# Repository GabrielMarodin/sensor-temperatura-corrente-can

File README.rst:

Monitoramento de temperatura e corrente via CAN do barco solar
#####################################################################

.. contents::
   :local:
   :depth: 2

Requisitos
**********

Este projeto foi implementado com os seguintes módulos/softwares/hardwares:
 | Sensor de temperatura PT100 com 3 fios.    
 | Sensor de corrente de efeito Hall LEM LA 205-S.  
 | MCP2515 (Controlador CAN);
 | TJA1050 (Transceptor CAN);  
 | Linguagem de programação C.  
 | Microcontrolador STM32F401 com SPI, ADC e regulador de 5V para 3V3.  

Visão geral
***********

Esse projeto faz parta do barco solar Zênite Solar.

.. figure:: /images/pcb_3dmodel.png
   :alt: Modelo 3D da placa de circuito impresso
   :align: center
   :name: 3D model of PCB.

É um sistema microcontrolado embarcado ao barco que possui capacidade de ler temperaturas em pontos estratégicos do barco e a corrente do motor.

O microcontrolador lê e trata os dados e empacota em um frame CAN para transmitir, através a implementação do controlador e transmissor CAN, para a saída do conector RJ45.

O desenvolvimento foi divido em quatro etapas:

- `Etapa 1 </etapa_1>`_ (02/04/2026): Pesquisa, planejamento e outline do projeto.
- `Etapa 2 </etapa_2>`_ (30/04/2026): Teste dos módulos e desenvolvimento de protótipo.
- `Etapa 3 </etapa_3>`_ (28/05/2026): Desenvolvimento do produto.
- `Etapa 4 </etapa_4>`_ (09/07/2026): Implementação e análise de desempenho.

Interface do usuário
********************
LED de respiração:
  Pisca enquanto o RTOS estiver ativo.

Testando
========

Para testar pode ser usado o debugger do microcontrolador para ler as variáveis e registradores ou um analizador de CAN para capturar as mensagens transmitidas.

Montagem
********

O sistema é alimentado e transmite os frames CAN pelo conector RJ45;

O sensor de corretente de efeito hall deve ser conectado no conector de 4 pinos;

O PT100 deve ser conectado no MAX31865 nos conectores de parafuso.

.. figure:: /images/max_3wired.jpg
   :alt: MAX31865 breakout board com 3 fios conectados
   :align: center
   :name: MAX31865 connection

   Modo de conexão de 3 fios do PT100.

   No modo 3 wires 2 fios estão em paralelo e 1 fio tem 100 ohms de resistência a 0 graus celsius em relação aos outros, os fios com resistência muito baixa entre si devem ser conectados em RTD+ e F+, enquanto o terceiro fio deve ser conectado em RTD-.

Referências (Links)
*******************

- `GitHub do Zênite Solar <https://github.com/ZeniteSolar>`_

- `Firmware do Projeto </etapa_4/Firmware>`_

- `Projeto KiCad da PCB </etapa_3/PCB/Modulo_corrente_temperatura_barco_Zenite>`_

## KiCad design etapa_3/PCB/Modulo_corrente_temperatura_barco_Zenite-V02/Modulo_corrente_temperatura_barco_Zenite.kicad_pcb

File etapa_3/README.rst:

Etapa 3
#######

.. contents::
   :local:
   :depth: 2

Visão geral
***********

A Etapa 3 abordará a implementação do protocolo CAN, bem como a integração e os testes dos dados provenientes dos sensores em um mesmo firmware baseado em arquitetura RTOS. O objetivo é validar o envio correto das informações pelo barramento CAN.

Além disso, será abordado a elaboração do esquemático da placa de circuito impresso, juntamente com a definição dos critérios de desempenho do sistema, que serão avaliados na etapa seguinte.

Desenvolvimento
***************

`Link para os Testes <Testes>`_

Implementação do Protocolo CAN
==============================

O `driver </etapa_3/Testes/pi3_CAN_test/Core/Src/MCP2515_driver.c>`_ do MCP2515 se baseia na implementação da Microchip e utiliza o mapa de registradores do  `datasheet <https://ww1.microchip.com/downloads/en/DeviceDoc/MCP2515-Stand-Alone-CAN-Controller-with-SPI-20001801J.pdf>`_ (tabelas 11-1 e 11-2).
O MCP2515 é configurado para ter sua divisão de clock de 8 MHz de forma a transmitir em 500 Kbps;

Integração dos dados dos sensores à aplicação
=============================================

Os dados dos sensores foram arranjados da seguinte maneira:

Temperatura:

+-------------------+----------------+
|        Dado       | Tamanho (Bits) |
+===================+================+
|    Temp. Motor    |       10       |
+-------------------+----------------+
| Temp. Controlador |       9        |
+-------------------+----------------+
|   Temp. Bateria   |       10       |
+-------------------+----------------+
|  Falha Detectada  |        3       |
+-------------------+----------------+

Foi alterado para possibilitar o relatório de erro individual de cada sensor.

Corrente:

+---------------------+----------------+
| Dado                | Tamanho (Bits) |
+=====================+================+
| Corrente de Pico    | 12             |
+---------------------+----------------+
| Sentido do Pico     | 1              |
+---------------------+----------------+
| Corrente RMS        | 12             |
+---------------------+----------------+
| Sentido da Corrente | 1              |
+---------------------+----------------+
| Mensagem de Erro    | 7              |
+---------------------+----------------+

Estes dados foram integrados em pacotes com o seguinte código:

`sensor de corrente </etapa_3/Firmware/Core/Inc/current_sensor.h>`_:

.. code-block:: C

	typedef struct __attribute__((packed)) {
      uint32_t Peak_Current : 11; // Corrente de Pico
      uint32_t Peak_Dir     : 1;  // Sentido da Corrente de Pico
      uint32_t Current_RMS  : 12; // Corrente RMS
      uint32_t Current_Dir  : 1;  // Direção Principal da Corrente
      uint32_t Error_msg    : 7;  // Mensagens de Erro
   } Current_pkg;

`sensores de temperatura </etapa_3/Firmware/Core/Inc/temperature_sensor.h>`_:

.. code-block:: C

   typedef struct __attribute__((packed)) {
      uint32_t Motor_Temp  : 10; // Temperatura do Motor
      uint32_t Charge_Temp : 9;  // Temperatura dos Controladores de Carga
      uint32_t Batt_Temp   : 10; // Temperatura da Bateria
      uint32_t Error_msg   : 3;  // Mensagens de Erro
   } Temp_pkg;

- `Link para o firmware </etapa_3/Firmware>`_

Teste da Rede CAN com Dados dos Sensores
========================================
Após implementação em código do `sensor de corrente </etapa_3/Testes/Sensor_RTOS/Core/Src/Current_Sensor.c>`_ 
e dos `sensores de temperatura </etapa_3/Testes/Sensor_RTOS/Core/Src/Temperature_Sensor.c>`_, foi implementada 
à partir do `driver do MCP2515 </etapa_3/Testes/Sensor_RTOS/Core/Src/MCP2515_Driver.c>`_ a transmição dos 
dados dos sensores utilizando o protocolo CAN nos IDS 0x10 e 0x11. O teste foi realizado utilizando um 
`ESP 32 </etapa_3/Testes/ESP32devkit/ESP32MCP2515>`_ como nó receptor, com o blackpill STM atuando como 
nó transmissor enviando mensagens.

Segue uma imagem do teste da rede CAN, o osciloscópio mede a tensão diferencial da linha no módulo utilizado.

.. image:: images/can_test.png
   :scale: 30 %

O ESP32 foi configurado para repassar as mensagems que recebe por SPI do MCP2515 para a porta 
serial, e o terminal do computador foi configurado para receber as mensagens. Devido à um problema de comunicação,
não foi possível realizar a leitura da rede CAN.

Esquemático da PCI
==================

O projeto KiCad onde foi elaborado o esquemático pode ser encontrado em:  `Link para o Esquemático do Projeto <https://github.com/GabrielMarodin/sensor-temperatura-corrente-can/tree/main/etapa_3/PCB/Modulo_corrente_temperatura_barco_Zenite>`_ 

O esquemático apresentado em partes nos próximos tópicos foi desenvolvido para atender aos requisitos do projeto, considerando:

- Níveis de tensão e corrente necessários para cada sensor e circuito integrado.

.. image:: images/Esquematico_potencia.png
	:scale: 30%

Na figura acima é possível observar elementos de proteção contra sobrecorrente e surtos de tensão, além de um regulador linear destinado à alimentação do microcontrolador e de um conversor estático responsável por suprir as necessidades do sensor de corrente utilizado.

- Conexão com a rede CAN, alimentação do módulo e do sensor de corrente.

.. image:: images/Esquematico_conectores.png
	:scale: 30%

Além dos conectores RJ45 padrão do barco foi necessário a previsão de um conector 3 pinos genérico para a alimentação e retorno do sinal em corrente do LA 205-s.

- Condicionamento do sinal de corrente do LA 205-s.

.. image:: images/Esquematico_condicionamento_sinal.png
	:scale: 30%

Observa-se na figura a presença de amplificadores operacionais configurados em diferentes topologias: buffer (para sinal de referência), somador não inversor (para obtenção do offset) e filtro ativo passa-baixa de segunda ordem.

   O circuito funciona de modo que:

   - 1,65 V na saída representam 0 A;
   - 3,3 V na saída correspondem a +200 A;
   - 0 V na saída equivalem a –200 A.
 
Ressalta-se que, atualmente, a frequência de corte do filtro encontra-se próxima de 120 kHz. No entanto, essa configuração pode ser ajustada posteriormente, mediante análise da forma de onda real da corrente do motor.

- Gerenciamento e envio de mensagens CAN.

.. image:: images/Esquematico_CAN.png
	:scale: 30%

Na figura acima obeserva-se os CIs responsáveis pelo gerenciamento do protocolo e transdução do sinal.

- Processamento de dados e transdução da temperatura.

.. image:: images/Esquematico_microcontrolador.png
	:scale: 30%

Na figura acima observa-se a atribuição dos pinos no microcontrolador, além dos três módulos baseados no circuito integrado MAX31865. Ressalta-se que existe a possibilidade de substituir os módulos pelo próprio CI, entretanto, devem ser consideradas as restrições de fabricação da placa em virtude do encapsulamento do MAX31865.

Critérios de Desempenho
***********************

Os critérios de desempenho adotados para o projeto, que deverão ser medidos na próxima etapa, são:

- Tempo de execução de cada tarefa;
- Tempo de ocupação da CPU;
- Medição do WCET (Worst-Case Execution Time);
- Eficiência energética da placa;
- Exatidão das medidas de corrente e temperatura, para fins de validação do código.

Referências (links/datasheets/livros)
*************************************

- `Código de interface MCP2515 <https://github.com/eziya/STM32_SPI_MCP2515/tree/master>`_

- `Datasheet do MCP2515 <https://www.microchip.com/en-us/product/mcp2515>`_

- `GitHub do Zenite Solar <https://github.com/ZeniteSolar>`_

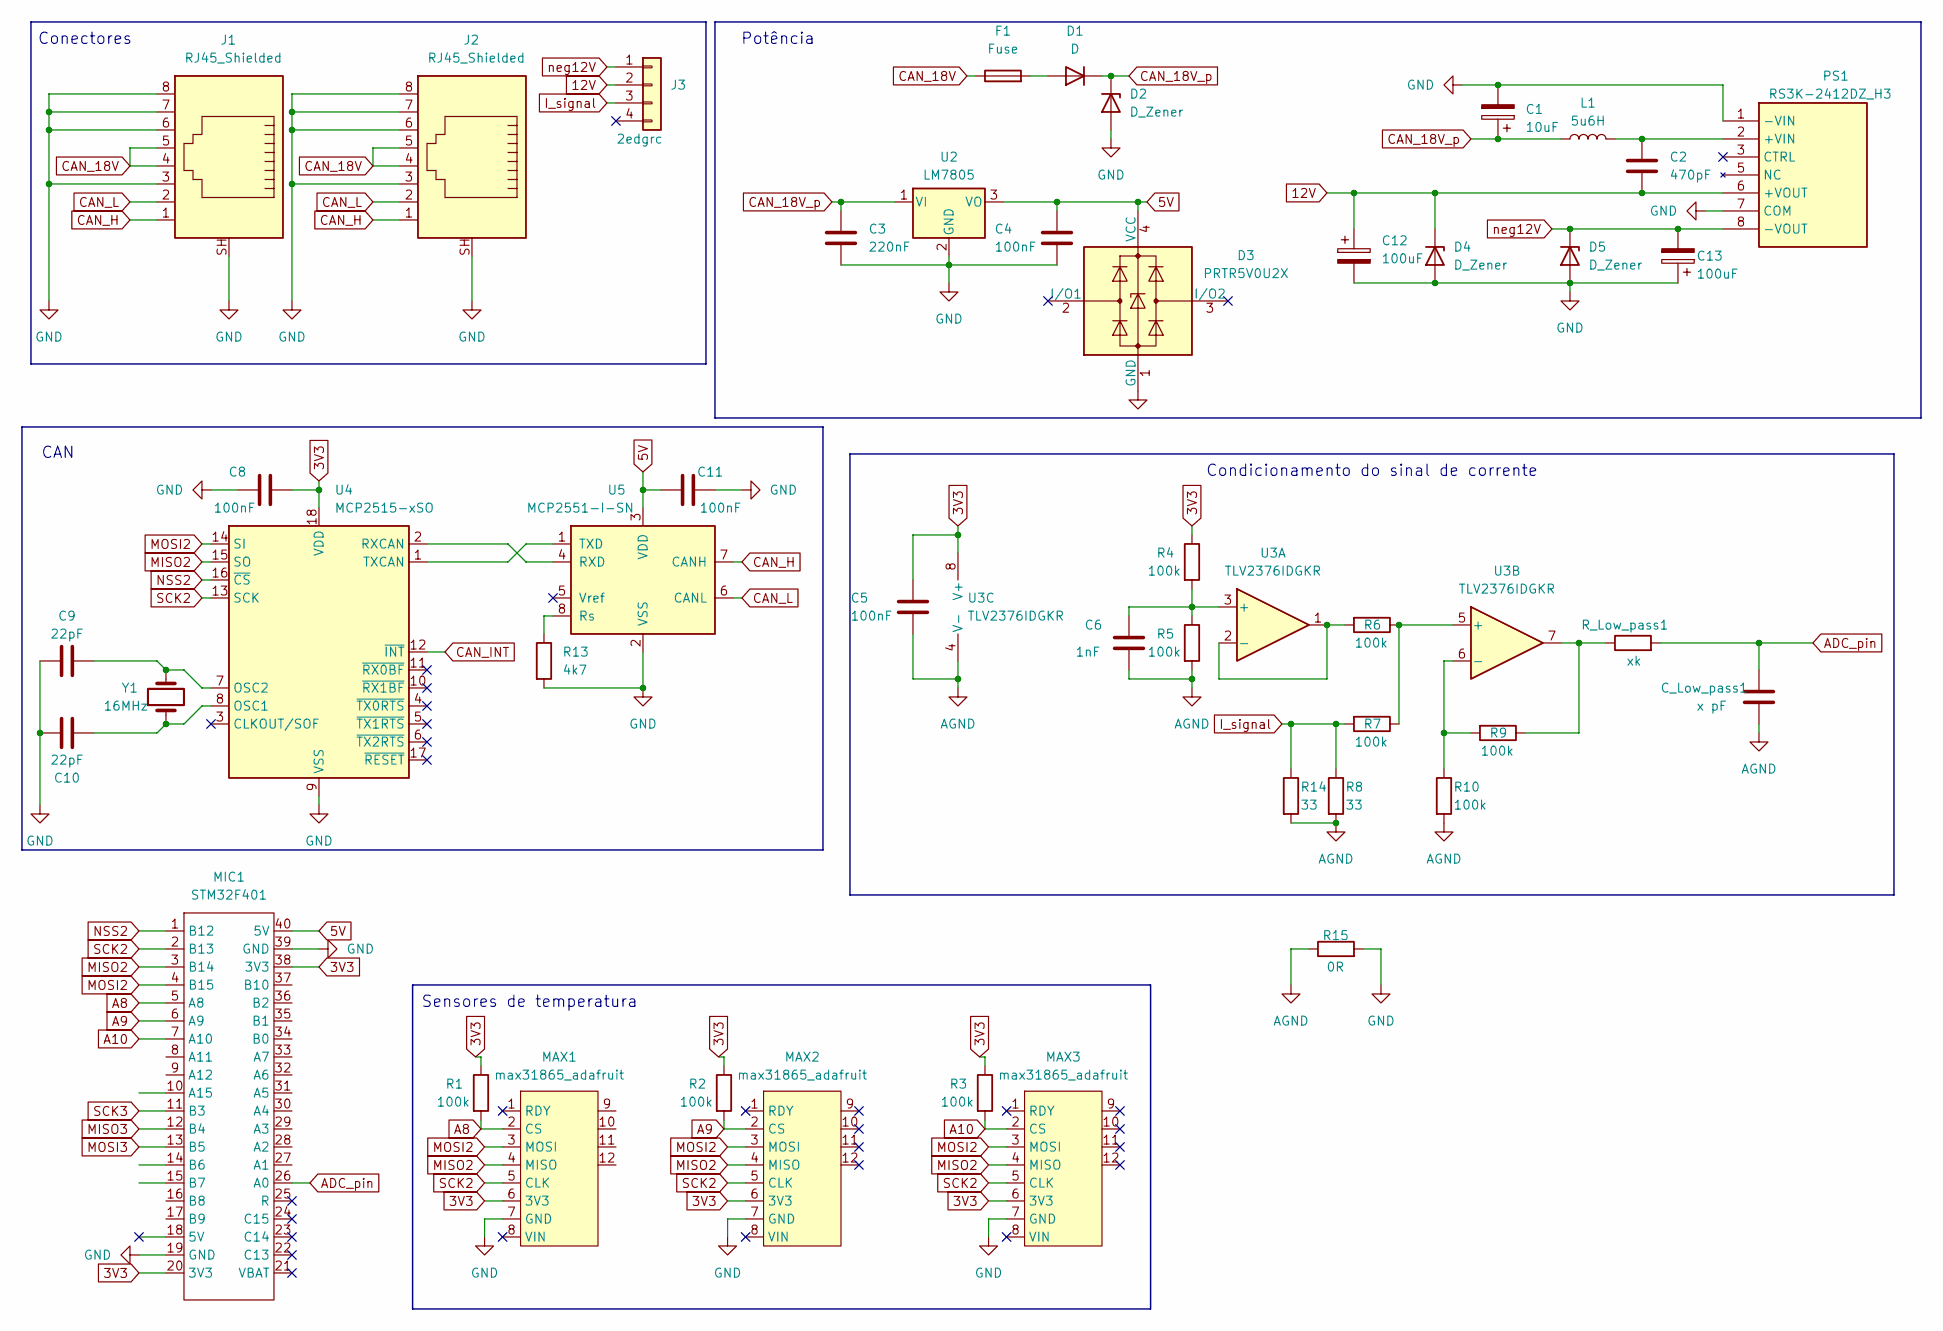
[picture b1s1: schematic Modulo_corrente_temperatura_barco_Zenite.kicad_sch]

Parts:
C1: 10uF; CP_Radial_D6.3mm_P2.50mm
C2: 470pF; C_0805_2012Metric_Pad1.18x1.45mm_HandSolder
C3: 220nF; C_0805_2012Metric_Pad1.18x1.45mm_HandSolder
C4, C5, C8, C11: 100nF; C_0805_2012Metric_Pad1.18x1.45mm_HandSolder
C6: 1nF; C_0805_2012Metric_Pad1.18x1.45mm_HandSolder
C9, C10: 22pF; C_0805_2012Metric_Pad1.18x1.45mm_HandSolder
C12, C13: 100uF; CP_Radial_D6.3mm_P2.50mm
C_Low_pass1: x pF; C_0805_2012Metric_Pad1.18x1.45mm_HandSolder
D1: D; D_5W_P10.16mm_Horizontal
D2: D_Zener; D_5W_P10.16mm_Horizontal
D3: PRTR5V0U2X; SOT-143_Handsoldering
D4, D5: D_Zener; D_SOD-123
F1: Fuse; fuse_holder
J1, J2: RJ45_Shielded; TE_RJ45-8N-B
J3: 2edgrc; 2EDRC_4pins
L1: 5u6H; ASPI0630LR5R6MT15
MAX1, MAX2, MAX3: max31865_adafruit; max31868_module
MIC1: STM32F401; BlackPill
PS1: RS3K-2412DZ_H3; RS3K2412DZH3; Manufacturer_Part_Number RS3K-2412DZ/H3
R1, R2, R3: 100k; R_Axial_DIN0207_L6.3mm_D2.5mm_P10.16mm_Horizontal
R4, R5, R6, R7, R9, R10: 100k; R_1206_3216Metric_Pad1.30x1.75mm_HandSolder
R8, R14: 33; R_1206_3216Metric_Pad1.30x1.75mm_HandSolder
R13: 4k7; R_0805_2012Metric_Pad1.20x1.40mm_HandSolder
R15: 0R; R_0805_2012Metric_Pad1.20x1.40mm_HandSolder
R_Low_pass1: xk; R_0805_2012Metric_Pad1.20x1.40mm_HandSolder
U2: LM7805; TO-220-3_Horizontal_TabDown
U3: TLV2376IDGKR; VSSOP-8_3x3mm_P0.65mm
U4: MCP2515-xSO; SOIC-18W_7.5x11.6mm_P1.27mm
U5: MCP2551-I-SN; SOIC-8_3.9x4.9mm_P1.27mm
Y1: 16MHz; Crystal_HC50_Vertical

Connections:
3V3: C5.1, C8.2, MAX1.6 (3V3), MAX2.6 (3V3), MAX3.6 (3V3), MIC1.20 (3V3), MIC1.38 (3V3), R1.1, R2.1, R3.1, R4.1, U3.8 (V+), U4.18 (VDD)
5V: C4.1, C11.1, D3.4 (VCC), MIC1.40 (5V), U2.3 (VO), U5.3 (VDD)
12V: C2.2, C12.1, D4.1 (K), J3.2, PS1.6 (+VOUT)
A8: MAX1.2 (CS), MIC1.5 (A8), R1.2
A9: MAX2.2 (CS), MIC1.6 (A9), R2.2
A10: MAX3.2 (CS), MIC1.7 (A10), R3.2
ADC_pin: C_Low_pass1.1, MIC1.26 (A0), R_Low_pass1.2
AGND: C5.2, C6.2, C_Low_pass1.2, R5.2, R8.2, R10.2, R14.2, R15.1, U3.4 (V-)
CAN_18V: F1.1, J1.4, J1.5, J2.4, J2.5
CAN_18V_p: C1.1, C3.1, D1.1 (K), D2.1 (K), L1.1, U2.1 (VI)
CAN_H: J1.1, J2.1, U5.7 (CANH)
CAN_INT: U4.12 (~INT)
CAN_L: J1.2, J2.2, U5.6 (CANL)
GND: C1.2, C3.2, C4.2, C8.1, C9.1, C10.1, C11.2, C12.2, C13.1, D2.2 (A), D3.1 (GND), D4.2 (A), D5.2 (A), J1.3, J1.6, J1.7, J1.8, J1.SH, J2.3, J2.6, J2.7, J2.8, J2.SH, MAX1.7 (GND), MAX2.7 (GND), MAX3.7 (GND), MIC1.19 (GND), MIC1.39 (GND), PS1.1 (-VIN), PS1.7 (COM), R13.2, R15.2, U2.2 (GND), U4.9 (VSS), U5.2 (VSS)
I_signal: J3.3, R7.2, R8.1, R14.1
MISO2: MAX1.4 (MISO), MAX2.4 (MISO), MAX3.4 (MISO), MIC1.3 (B14), U4.15 (SO)
MISO3: MIC1.12 (B4)
MOSI2: MAX1.3 (MOSI), MAX2.3 (MOSI), MAX3.3 (MOSI), MIC1.4 (B15), U4.14 (SI)
MOSI3: MIC1.13 (B5)
NSS2: MIC1.1 (B12), U4.16 (~CS)
unnamed: D1.2 (A), F1.2
unnamed: C2.1, L1.2, PS1.2 (+VIN)
unnamed: R9.1, R_Low_pass1.1, U3.7
unnamed: C6.1, R4.2, R5.1, U3.3 (+)
unnamed: R6.2, U3.1, U3.2 (-)
unnamed: R6.1, R7.1, U3.5 (+)
unnamed: R9.2, R10.1, U3.6 (-)
unnamed: C10.2, U4.8 (OSC1), Y1.1
unnamed: C9.2, U4.7 (OSC2), Y1.2
unnamed: U4.2 (RXCAN), U5.4 (RXD)
unnamed: U4.1 (TXCAN), U5.1 (TXD)
unnamed: R13.1, U5.8 (Rs)
SCK2: MAX1.5 (CLK), MAX2.5 (CLK), MAX3.5 (CLK), MIC1.2 (B13), U4.13 (SCK)
SCK3: MIC1.11 (B3)
neg12V: C13.2, D5.1 (K), J3.1, PS1.8 (-VOUT)

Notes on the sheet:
Sensores de temperatura
Conectores
CAN
Condicionamento do sinal de corrente
Potência

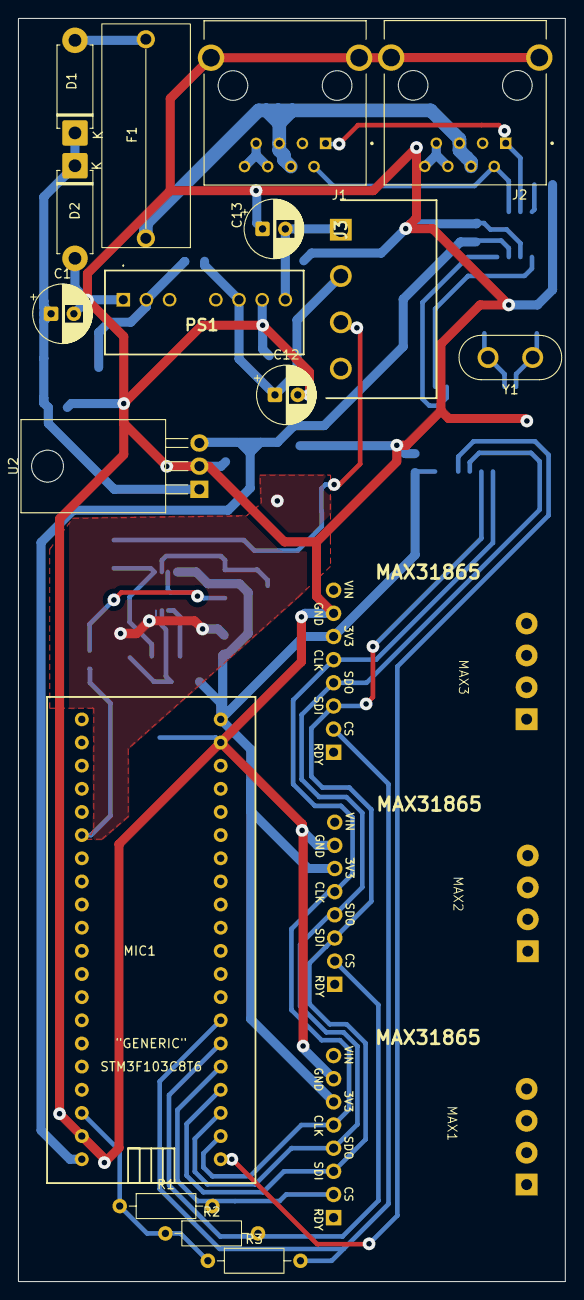
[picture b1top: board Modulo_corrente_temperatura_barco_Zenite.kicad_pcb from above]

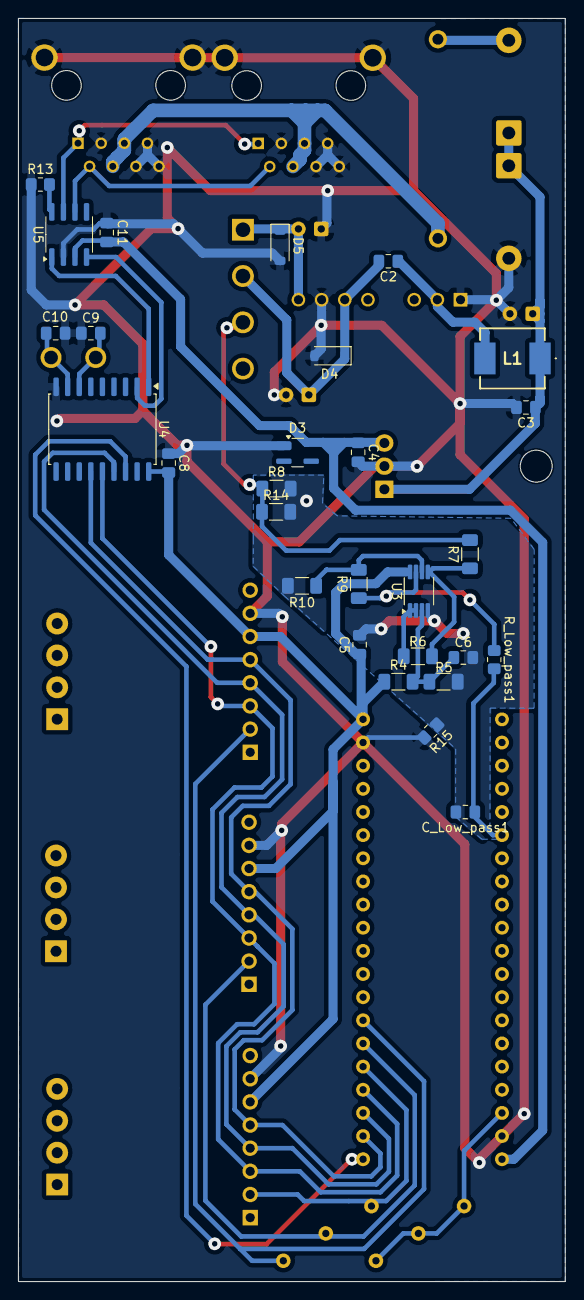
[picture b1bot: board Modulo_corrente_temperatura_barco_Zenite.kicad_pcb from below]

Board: 2 copper layers, 60.0 x 138.6 mm, 47 parts (28 on the bottom side), 31 nets.

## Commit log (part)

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2026-03-18 modified: Requisitos do sistema.pdf
2026-03-25 Revise README with project overview and requirements
    Expand the overview and requirements for the embedded system project, detailing functional and non-functional requirements, technologies, and components needed for the development of the Guarapuvu II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
2026-03-27 images to documentation purposes
2026-03-28 Revise requirements and specifications in README
    Updated functional requirements and specifications for temperature and current measurement, including specific sensor and microcontroller details. Revised signal conversion and CAN communication deta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
2026-03-30 Revise requirements and specifications in README
    Updated functional requirements for temperature and current measurements, including precision and frequency specifications. Enhanced signal conversion and communication details.
2026-03-30 Hall sensor photo
2026-03-30 Update README to include temperature in CAN transmission
2026-03-30 Update README.rst
    etapas de desenvolvimento
2026-03-30 fluxograma
2026-03-30 Update README.rst
    adicionado fluxograma
2026-03-30 Delete etapa_1/images/lanes_flowchart.png
    imagem melhor a ser adicionada
2026-03-30 Add files via upload
    jpeg com fundo branco
2026-03-30 Update README.rst
    flowchart
2026-04-01 Rename Diagrama do Barco.drawio.png to Diagrama_do_Barco.png
2026-04-01 Adjust image scales and enhance CAN communication details
    Updated image scales and added details on current measurements in the CAN communication section.
2026-04-15 código de teste para o sensor de temperatura
2026-04-15 archive file
2026-04-16 refactored for multiple devices
2026-04-16 update archive
2026-04-22 project documentation update
2026-04-22 improve README clarity
2026-04-22 Update frequency values in README
2026-04-24 Update README.rst - Descrição Básica
    Adicionada descrição básica sobre os testes
    Falta:
    - Testar ADC com o sensor e o amplificador
    - Adicionar imagens
    - Detalhar melhor o que foi feito nos laboratórios
    - Testar para correntes negativas com a fonte linear (V < 3.3/2)
2026-04-27 resultados práticos e código funcional
2026-04-29 CAN documentation update and screenshots upload
2026-04-29 images Pt100
2026-04-29 Update README.rst
    Pt100 images
2026-04-29 Update README.rst
    scale
2026-04-29 Update README.rst
    size
2026-04-29 Update README.rst
    Adicionados detalhes do teste do sensor ADC - junto com cálculos básicos e imagens dos resultados
2026-04-29 Fix formatting of current values in README
2026-04-30 Update README.rst
    Melhoras na descrição dos testes e implementação do sensor de corrente
2026-04-30 Update main.c
    Bit shift corrigido para dividir - medida de corrente espelhada para o primário
2026-04-30 Fix typos in README.rst
2026-04-30 Fix typos in README.rst
    Corrige a palavra 'referênte' para 'referente' e remove espaço extra na seção de Desenvolvimento.
2026-04-30 code optimization
2026-04-30 Add documentation links for LA 205-S and MAX31865
    Added documentation links for LA 205-S and MAX31865.
2026-04-30 Fix formatting of documentation links in README
2026-04-30 Update CAN version from 2.0B to 2.0A in README
2026-05-02 Preliminary module schematic added
2026-05-02 sallen-key filter fixed to match 0.707 quality factor
2026-05-05 Fix data types and formatting in README
2026-05-10 Primeiro Protótipo da Comunicação dos Sensores
    Código ainda não foi testado devido à problemas locais com a geração/compilação de código, provavelmente devido à má configuração do CubeIDE e do CubeMX
2026-05-10 Update README.rst
    Adicionada referência do código SPI->MCP2515
2026-05-11 MCP2515_driver and code for test added
2026-05-11 Fix TX buffer selection and update transmission data
2026-05-12 RTOS
2026-05-12 can tasks wireframes
2026-05-13 Update MCP2515.c
    Troacado de SPI1 para SPI2
2026-05-13 Update Sensors.c
    Adicionada linha para transmitir pacote por CAN
2026-05-13 Update MCP2515_Config with alternative baud rate settings
    Commented out alternative configuration for 8 MHz crystal.
2026-05-13 esp32 arduino can receiver build
2026-05-14 esp32 serial print
2026-05-14 read all dataframe
2026-05-20 Implementados Sensores em RTOS
    Adicionados arquivos dos sensores de corrente e temperatura, incluindo montar os pacotes.
    Falta implementar o protocolo CAN
2026-05-21 obfuscated tasks into their drivers, implemented queues
2026-05-21 pinout update
2026-05-21 Mount pkg and send via SPI functions added for sensors libs
2026-05-21 Projeto Inicial do Filtro
    Cálculo dos coeficientes de um filtro butter, com simulação do resultado final e coeficientes do filtro em SOS para aplicação por CMSIS
2026-05-21 Melhora na Simulação
    Plots mais claras e simulando cenário mais próximo da realidade
2026-05-21 CAN device handle integration
2026-05-23 Adicionado FFT do filtro
    Adicionado plot do FFT do filtro butterworth nas frequências que serão medidas
2026-05-23 Update README.rst
    Adicionado esqueleto do teste da rede CAN
    Falta:
    - Comparativo entre dados enviados e recebidos
    - Detalhes sobre a placa
    - Falar sobre a implementação dos sensores de corrente e temperatura, incluindo cálculos
2026-05-24 Document CAN protocol and sensor integration
    Added documentation for CAN protocol implementation and sensor data integration.
2026-05-24 update README with Schematics and performance criteria
2026-05-24 Fix formatting issues in README.rst
2026-05-24 Ajustar referências e texto no README
    Corrigido o formato das referências aos arquivos de código e melhorada a clareza do texto.
2026-05-24 Corrigido Erro no Link do Código do ESP32
2026-05-24 Update schematic project link in README
2026-05-24 Fix file paths in CAN test section of README
    Updated file paths in README for CAN network test documentation.
2026-05-25 changed bitfield packing
2026-05-26 added breathing LED, changed SCLK to PB13
2026-05-26 same as previous
2026-05-26 Adicionada Imagem do Osciloscópio
2026-05-26 Corrigida Escala da Imagem
2026-05-26 minor adjustments
2026-05-28 Adicionada Documentação dos Sensores
    Adicionadas tabelas e blocos de código na documentação da integração dos sensores
2026-05-28 Concertadas Tabelas
2026-05-28 Concertada Tabela de Novo
2026-05-28 Concertando a tabela mais uma vez
2026-05-28 Increase Charge_Temp bit field size to 10 bits
2026-05-28 Update Charge_Temp bit field size in README
2026-05-28 Update sensor data structure and sizes in README
    Altered the bit sizes for the controller temperature and error message fields to allow for individual sensor error reporting.
2026-05-28 CAN tests Tx Rx
2026-05-28 C:/Program Files/Git/
2026-05-28 imagens
2026-05-28 Update README with implementation details and references
    Removed outdated content and added references to MCP2515 datasheet and Zenite Solar GitHub.
2026-06-07 PCB layout V1 added - DRC review nedded
2026-06-25 Capacitores ajustados
    Corrijido erro DRC
2026-06-26 Updated PCB version - DRC and final routing needed
2026-06-28 minor ajustmentes in PCB laytout and schem
2026-06-30 Roteamento do AmpOP
    Roteamento do AMpOP na v2.0 da placa - ainda verificando melhorias
2026-06-30 ampop traces modified
